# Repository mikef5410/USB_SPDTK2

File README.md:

## USB_SPDTK (KiCAD)

USB control of two standard microwave SPDT coax switches. This is the KiCAD re-work for JLCPCB assembly.

Related projects: [my USB Dual SPDT project](https://github.com/mikef5410/USB_SPDT)  and  [the software for these projects](https://github.com/mikef5410/USB_Attenuator_Switch_Stacklight)

# Project setup

The software is included here as a git submodule. After cloning, do a
`git submodule init` followed by `git submodule update --recursive`

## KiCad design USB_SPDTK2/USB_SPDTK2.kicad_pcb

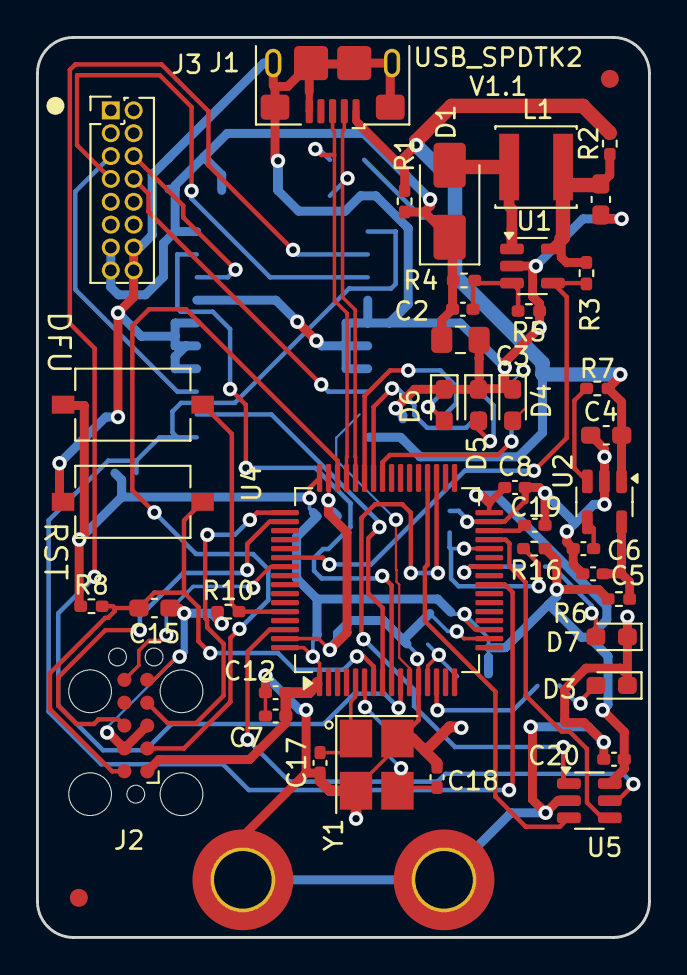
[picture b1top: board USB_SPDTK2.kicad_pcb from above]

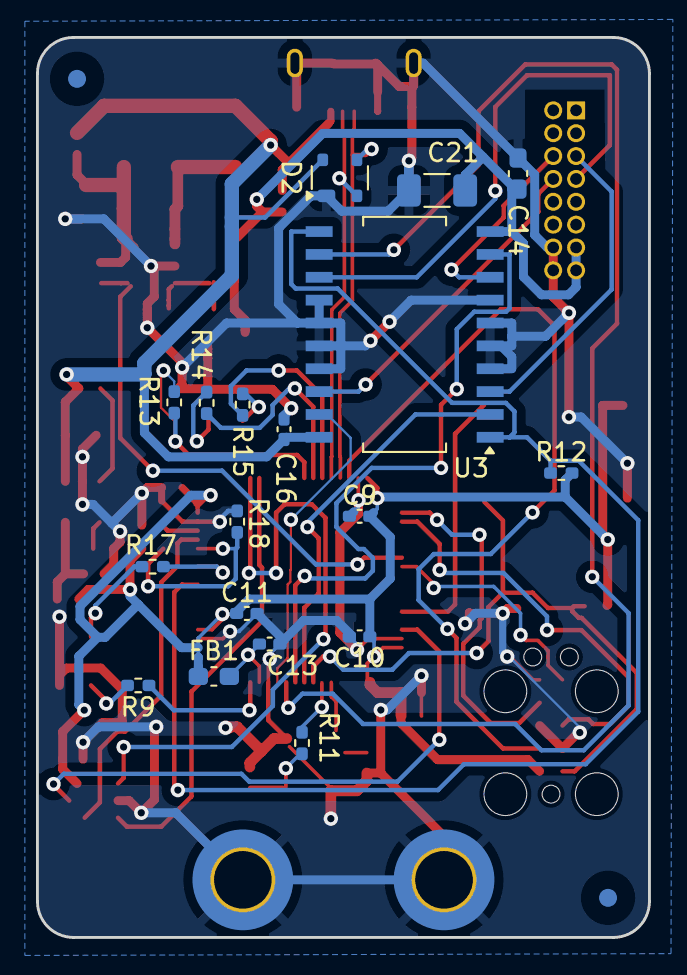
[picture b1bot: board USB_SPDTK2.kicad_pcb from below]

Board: 2 copper layers, 34.0 x 50.0 mm, 65 parts (20 on the bottom side), 48 nets.

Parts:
C1, C4, C14, C15: 1u; C_0603_1608Metric_Pad1.08x0.95mm_HandSolder
C2: 220p; C_0402_1005Metric_Pad0.74x0.62mm_HandSolder
C3: 4.7u; C_0805_2012Metric_Pad1.18x1.45mm_HandSolder
C5, C7, C19: 4.7u; C_0402_1005Metric_Pad0.74x0.62mm_HandSolder
C6, C8, C9, C10, C11, C12, C13, C16, C20: 0.1u; C_0402_1005Metric_Pad0.74x0.62mm_HandSolder
C17, C18: 30pF; C_0402_1005Metric_Pad0.74x0.62mm_HandSolder
C21: 22uF; C_1206_3216Metric_Pad1.33x1.80mm_HandSolder
D1: SS34; D_SMA
D2: PRTR5V0U2X; SOT-143
D3, D4, D5, D6: RED; LED_0603_1608Metric_Pad1.05x0.95mm_HandSolder
D7: GRN; LED_0603_1608Metric_Pad1.05x0.95mm_HandSolder
FB1: MMZ1608Y102B; C_0603_1608Metric_Pad1.08x0.95mm_HandSolder
FID1, FID2, FID3, FID4: Fiducial; Fiducial_1mm_Mask3mm
H1, H2: MountingHole_Pad; MountingHole_3.2mm_M3_DIN965_Pad_TopBottom
J1: USB_B_Micro; USB_Micro-B_Amphenol_10118193-0001LF_Horizontal
J2: TagConnectTC2050; Tag-Connect_TC2050-IDC-FP_2x05_P1.27mm_Vertical
J3: Conn_02x08_Odd_Even; PinHeader_2x08_P1.27mm_Vertical
L1: 10u; L_Changjiang_FNR4030S
R1, R2, R6: 0; R_0402_1005Metric_Pad0.72x0.64mm_HandSolder
R3, R7, R8, R10, R12, R16: 10k; R_0402_1005Metric_Pad0.72x0.64mm_HandSolder
R4: 118k; R_0402_1005Metric_Pad0.72x0.64mm_HandSolder
R5: 13.3k; R_0402_1005Metric_Pad0.72x0.64mm_HandSolder
R9, R11, R13, R14, R15, R17, R18: 100; R_0402_1005Metric_Pad0.72x0.64mm_HandSolder
SW1, SW2: SW_Push; SW_Tactile_SPST_NO_Straight_CK_PTS636Sx25SMTRLFS
U1: LM27313XMF; SOT-23-5
U2: LP2985-3.3; SOT-23-5
U3: L293DD; SO-20_12.8x7.5mm_P1.27mm
U4: STM32F411RETx; LQFP-64_10x10mm_P0.5mm
U5: 93LC66AT-IOT; SOT-23-6
Y1: 16M 20pF 3225; Crystal_SMD_3225-4Pin_3.2x2.5mm_HandSoldering

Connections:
+3.3V: C7.1, C8.1, C9.2, C10.1, C11.1, C12.2, C20.2, FB1.1, J2.1 (VTref), R6.2, R8.1, R12.2, R16.1, SW2.2, U4.1 (VBAT), U4.19 (VDD), U4.32 (VDD), U4.48 (VDD), U4.64 (VDD), U5.6 (Vcc)
+VSW: C2.1, C3.2, C14.2, C21.1, D1.1 (K), J3.13, J3.15, R1.2, R4.2, U3.10 (VCC2)
/Controller/BOOT1: R16.2, R18.1, U4.28 (PB2)
/Controller/JTCK: J2.4 (SWCLK/TCK), U4.49 (PA14)
/Controller/JTDI: J2.8 (NC/TDI), U4.50 (PA15)
/Controller/JTDO: J2.6 (SWO/TDO), U4.55 (PB3)
/Controller/JTMS: J2.2 (SWDIO/TMS), U4.46 (PA13)
/Controller/SPI2_MISO: U4.35 (PB14), U5.1 (DO)
/Controller/SPI2_MOSI: U4.36 (PB15), U5.3 (DI)
/Controller/SPI2_SCK: U4.29 (PB10), U5.4 (CLK)
/Controller/USB+: D2.3 (I/O2), J1.3 (D+), U4.45 (PA12)
/Controller/USB-: D2.2 (I/O1), J1.2 (D-), U4.44 (PA11)
/Controller/~SPI2NSS: U4.62 (PB9), U5.5 (CS)
GND: C1.1, C3.1, C4.1, C5.1, C6.1, C7.2, C8.2, C9.1, C10.2, C11.2, C12.1, C13.2, C14.1, C15.1, C16.1, C17.2, C18.2, C19.1, C20.1, C21.2, D2.1 (GND), D3.1 (K), D4.1 (K), D5.1 (K), D6.1 (K), D7.1 (K), H1.1, H2.1, J1.5 (GND), J1.6 (Shield), J2.3 (GND), J2.5 (GND), J2.9 (GNDDetect), J3.14, J3.16, R5.1, R10.1, R18.2, SW1.2, U1.2 (GND), U2.2 (GND), U3.4 (GND), U3.5 (GND), U3.6 (GND), U3.7 (GND), U3.14 (GND), U3.15 (GND), U3.16 (GND), U3.17 (GND), U4.12 (VSSA), U4.18 (VSS), U4.31 (VSS), U4.47 (VSS), U4.63 (VSS), U5.2 (Vss), Y1.2, Y1.4
HVEnable: R3.1, U1.4 (EN), U4.54 (PD2)
unnamed: C18.1, R11.1, Y1.3
unnamed: D1.2 (A), L1.2, U1.1 (SW)
unnamed: D3.2 (A), R9.2
unnamed: D4.2 (A), R13.2
unnamed: D5.2 (A), R14.2
unnamed: D6.2 (A), R15.2
unnamed: D7.2 (A), R17.2
unnamed: C15.2, J2.10 (~RESET), R8.2, SW1.1, U4.7 (NRST)
unnamed: C2.2, R4.1, R5.2, U1.3 (FB)
unnamed: C1.2, L1.1, R2.1, R3.2, U1.5 (VIN)
unnamed: C6.2, U2.4 (BP)
unnamed: R7.2, U2.3 (ON/~OFF)
unnamed: C5.2, R6.1, U2.5 (VOUT)
unnamed: R10.2, SW2.1, U4.60 (BOOT0)
unnamed: R9.1, U4.14 (PA0)
unnamed: R13.1, U4.41 (PA8)
unnamed: R14.1, U4.42 (PA9)
unnamed: R15.1, U4.43 (PA10)
unnamed: R17.1, U4.26 (PB0)
unnamed: C17.1, U4.5 (PH0), Y1.1
unnamed: R11.2, U4.6 (PH1)
unnamed: C19.2, U4.30 (VCAP1)
unnamed: C13.1, FB1.2, U4.13 (VDDA)
S1D: U3.9 (2A), U4.9 (PC1)
S1D_OUT: J3.6, U3.8 (2Y)
S1U: U3.2 (1A), U4.8 (PC0)
S1U_OUT: J3.5, U3.3 (1Y)
S2D: U3.19 (4A), U4.11 (PC3)
S2D_OUT: J3.8, U3.18 (4Y)
S2U: U3.12 (3A), U4.10 (PC2)
S2U_OUT: J3.7, U3.13 (3Y)
SW_Enable: R12.1, U3.1 (EN1,2), U3.11 (EN3,4), U4.24 (PC4)
VBUS: C4.2, C16.2, D2.4 (VCC), J1.1 (VBUS), R1.1, R2.2, R7.1, U2.1 (VIN), U3.20 (VCC1)

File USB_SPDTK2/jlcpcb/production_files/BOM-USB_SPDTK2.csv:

Comment,Designator,Footprint,LCSC,Quantity
4.7u,"C19,C5,C7",C_0402_1005Metric_Pad0.74x0.62mm_HandSolder,C106859,3
MMZ1608Y102B,FB1,C_0603_1608Metric_Pad1.08x0.95mm_HandSolder,C114771,1
SW_Push,"SW1,SW2",SW_Tactile_SPST_NO_Straight_CK_PTS636Sx25SMTRLFS,C118141,2
13.3k,R5,R_0402_1005Metric_Pad0.72x0.64mm_HandSolder,C122547,1
GRN,D7,LED_0603_1608Metric_Pad1.05x0.95mm_HandSolder,C125094,1
22uF,C21,C_1206_3216Metric_Pad1.33x1.80mm_HandSolder,C12891,1
LP2985-3.3,U2,SOT-23-5,C129375,1
USB_B_Micro,J1,USB_Micro-B_Amphenol_10118193-0001LF_Horizontal,C132562,1
1u,"C1,C14,C15,C4",C_0603_1608Metric_Pad1.08x0.95mm_HandSolder,C15849,4
220p,C2,C_0402_1005Metric_Pad0.74x0.62mm_HandSolder,C1603,1
30pF,"C17,C18",C_0402_1005Metric_Pad0.74x0.62mm_HandSolder,C1658,2
10u,L1,L_Changjiang_FNR4030S,C167879,1
0,"R2,R6",R_0402_1005Metric_Pad0.72x0.64mm_HandSolder,C17168,2
4.7u,C3,C_0805_2012Metric_Pad1.18x1.45mm_HandSolder,C1779,1
L293DD,U3,SO-20_12.8x7.5mm_P1.27mm,C21610,1
100,"R11,R13,R14,R15,R17,R18,R9",R_0402_1005Metric_Pad0.72x0.64mm_HandSolder,C25076,7
10k,"R10,R12,R7,R8",R_0402_1005Metric_Pad0.72x0.64mm_HandSolder,C25744,4
118k,R4,R_0402_1005Metric_Pad0.72x0.64mm_HandSolder,C25748,1
PRTR5V0U2X,D2,SOT-143,C2827688,1
LM27313XMF,U1,SOT-23-5,C341750,1
93LC66AT-IOT,U5,SOT-23-6,C511344,1
0.1u,"C10,C11,C12,C13,C16,C20,C6,C8,C9",C_0402_1005Metric_Pad0.74x0.62mm_HandSolder,C5142567,9
16M 20pF 3225,Y1,Crystal_SMD_3225-4Pin_3.2x2.5mm_HandSoldering,C524727,1
RED,"D3,D4,D5,D6",LED_0603_1608Metric_Pad1.05x0.95mm_HandSolder,C84263,4
SS34,D1,D_SMA,C8678,1
STM32F411RETx,U4,LQFP-64_10x10mm_P0.5mm,C94355,1
Conn_02x08_Odd_Even,J3,PinHeader_2x08_P1.27mm_Vertical,,1

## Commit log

2024-07-22 Initial
2024-08-01 Add do not fab warnings. L293D pinout is incorrect.
2024-10-08 Update to v1.1, fix incorrect footprint for L293DD
2024-10-10 Fix connector and C21 interference.
2024-11-04 Submitted to JLCPCB. Needed an in-stock part for D7
